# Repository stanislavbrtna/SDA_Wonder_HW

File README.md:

# SDA Mk. 2 Hardware Sources
In the Board directory are KiCad project files for the Boards used in the SDA and in the case Directory there are FreeCAD files for the SDA case. You can find more info about the SDA Project on its [project page](https://hackaday.io/project/35165-sda-the-best-new-pda) on hackaday.io.

## Known Bugs - Rev2b (current)

 1. SD card slot casing is not grounded on the pcb, sd card insertion detection doesn't work because of it. This can be fixed by scraping off the protective mask near the pin and bridging ground and shielding  with a bit of solder.
 2. Pads for battery connector are too small and can be ripped out of place when device falls form sufficient height. This is sort-of fixed with second revision of the case by giving the battery better support.
 3. The stacked PCBs are a point of failure, stress is built up in the connecting pins during soldering. This stress can break the contacts after few years of use, temperature changes, drops of the device. Luckily, re-soldering these pins is an easy job.

## Known Bugs - Rev1

 1. Vcc is used as Vref, if battery goes under 3.3V, then ADC measurements are wrong.
 2. There is no under-voltage protection at the moment.
 3. There is currently no guide for battery connector alignment, if battery connector is misaligned battery doesn't make good contact. 

## Case R2 notes
Second revision was printed and tested. It contains optional holes for a speaker and a microphone. The add-on module and cradle works well. 

## Case notes
 Only the 3D printable case for SDA was printed and tested, the FreeCAD file also contains drawings of a cradle and an add-on module, those are still work-in progress.

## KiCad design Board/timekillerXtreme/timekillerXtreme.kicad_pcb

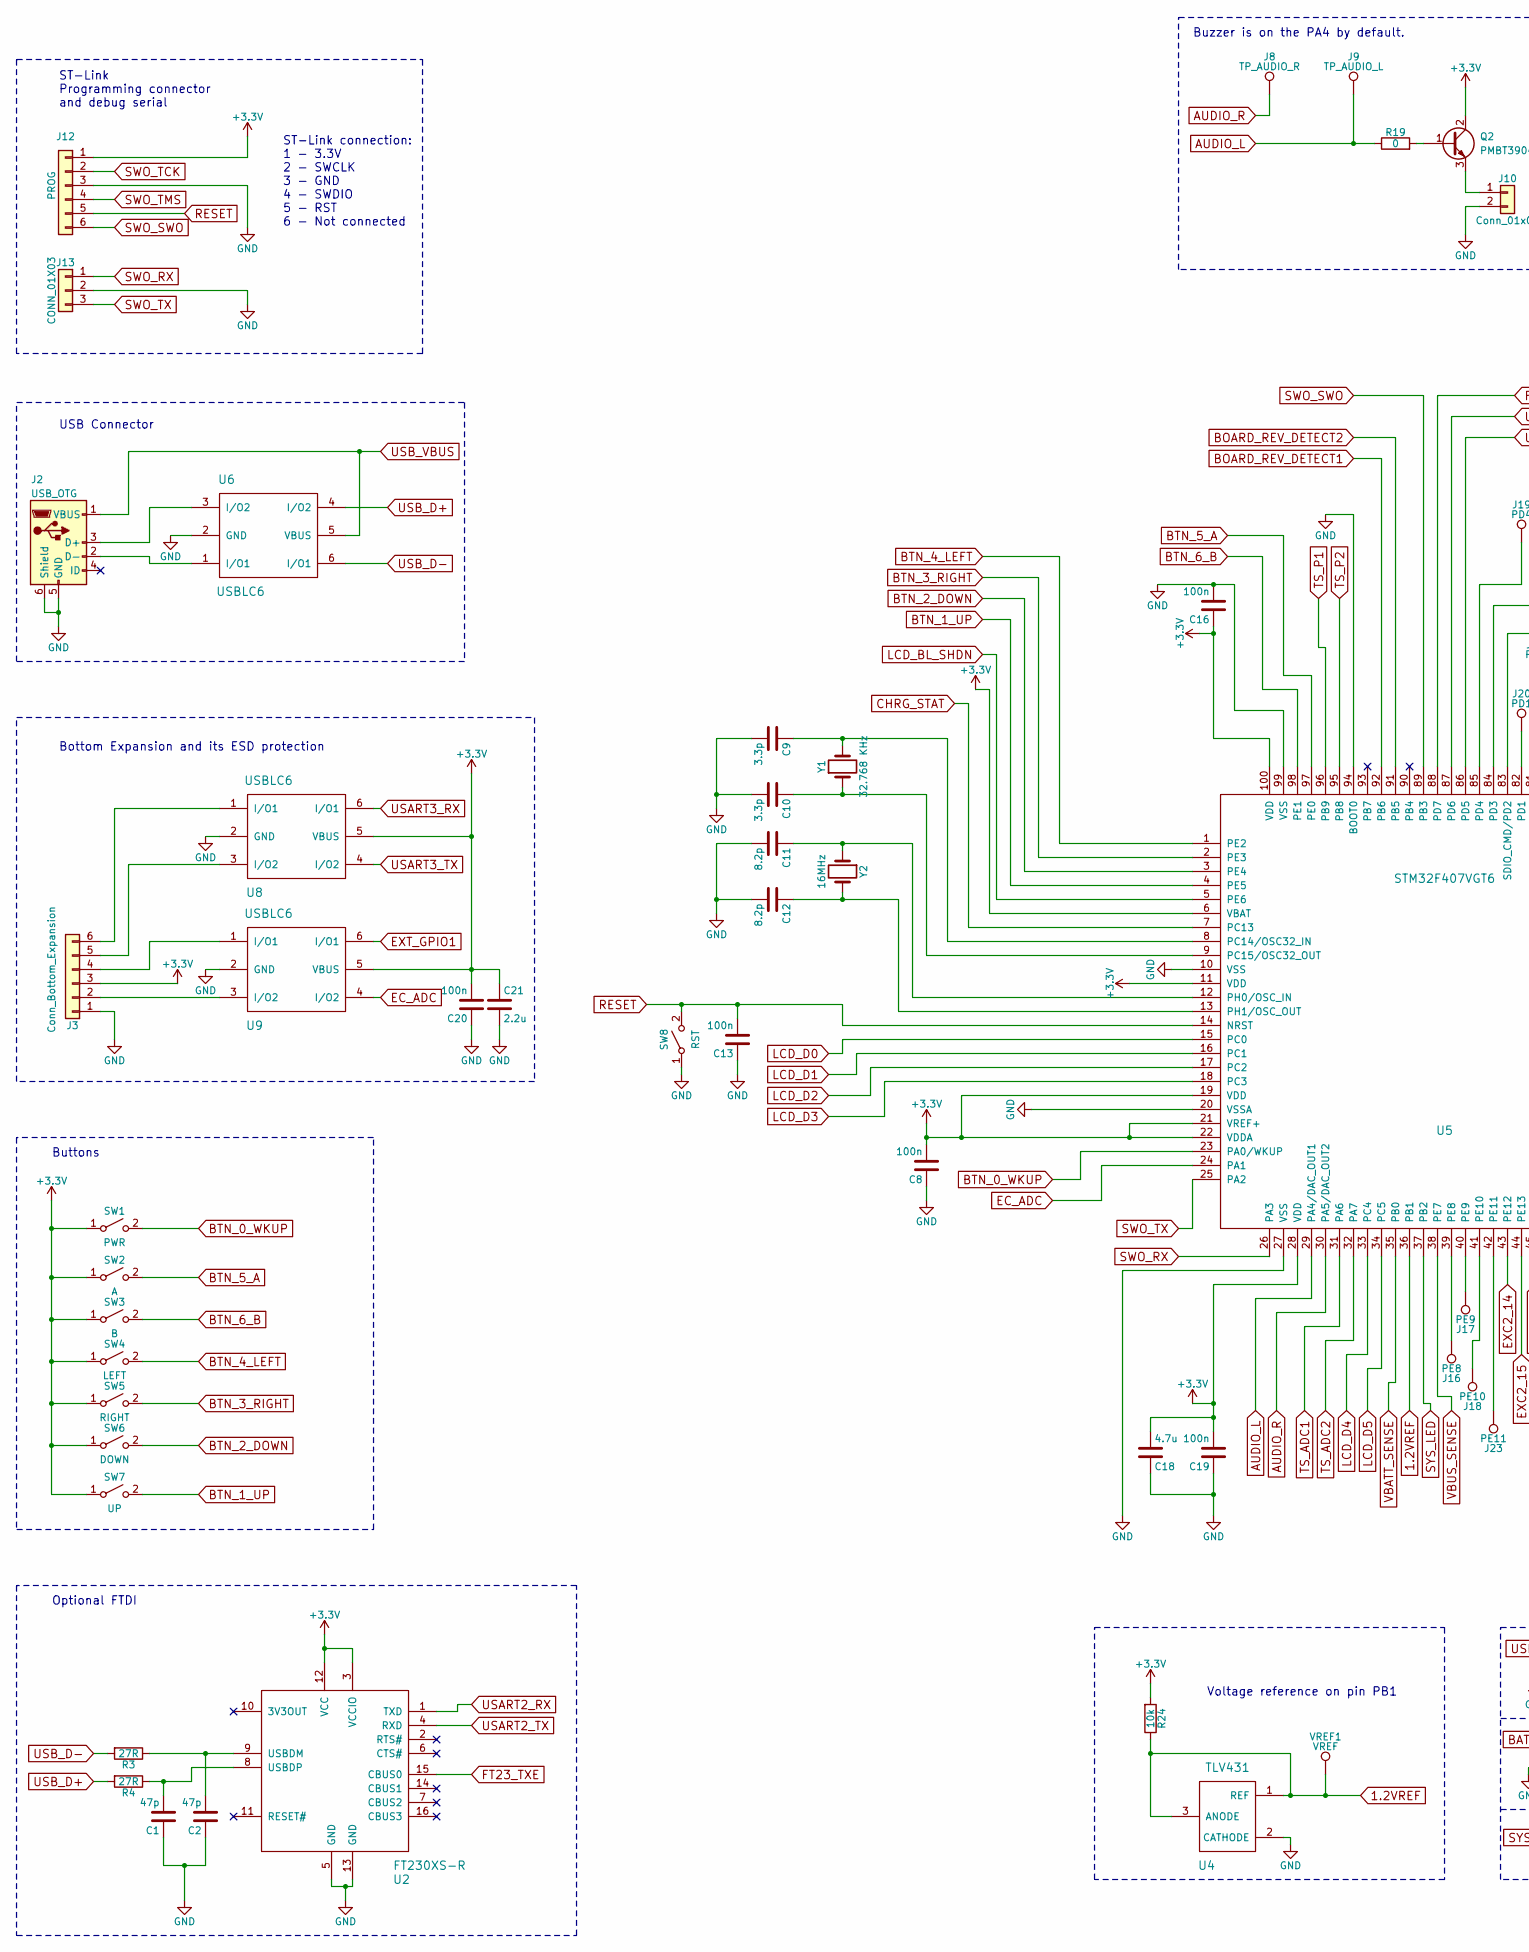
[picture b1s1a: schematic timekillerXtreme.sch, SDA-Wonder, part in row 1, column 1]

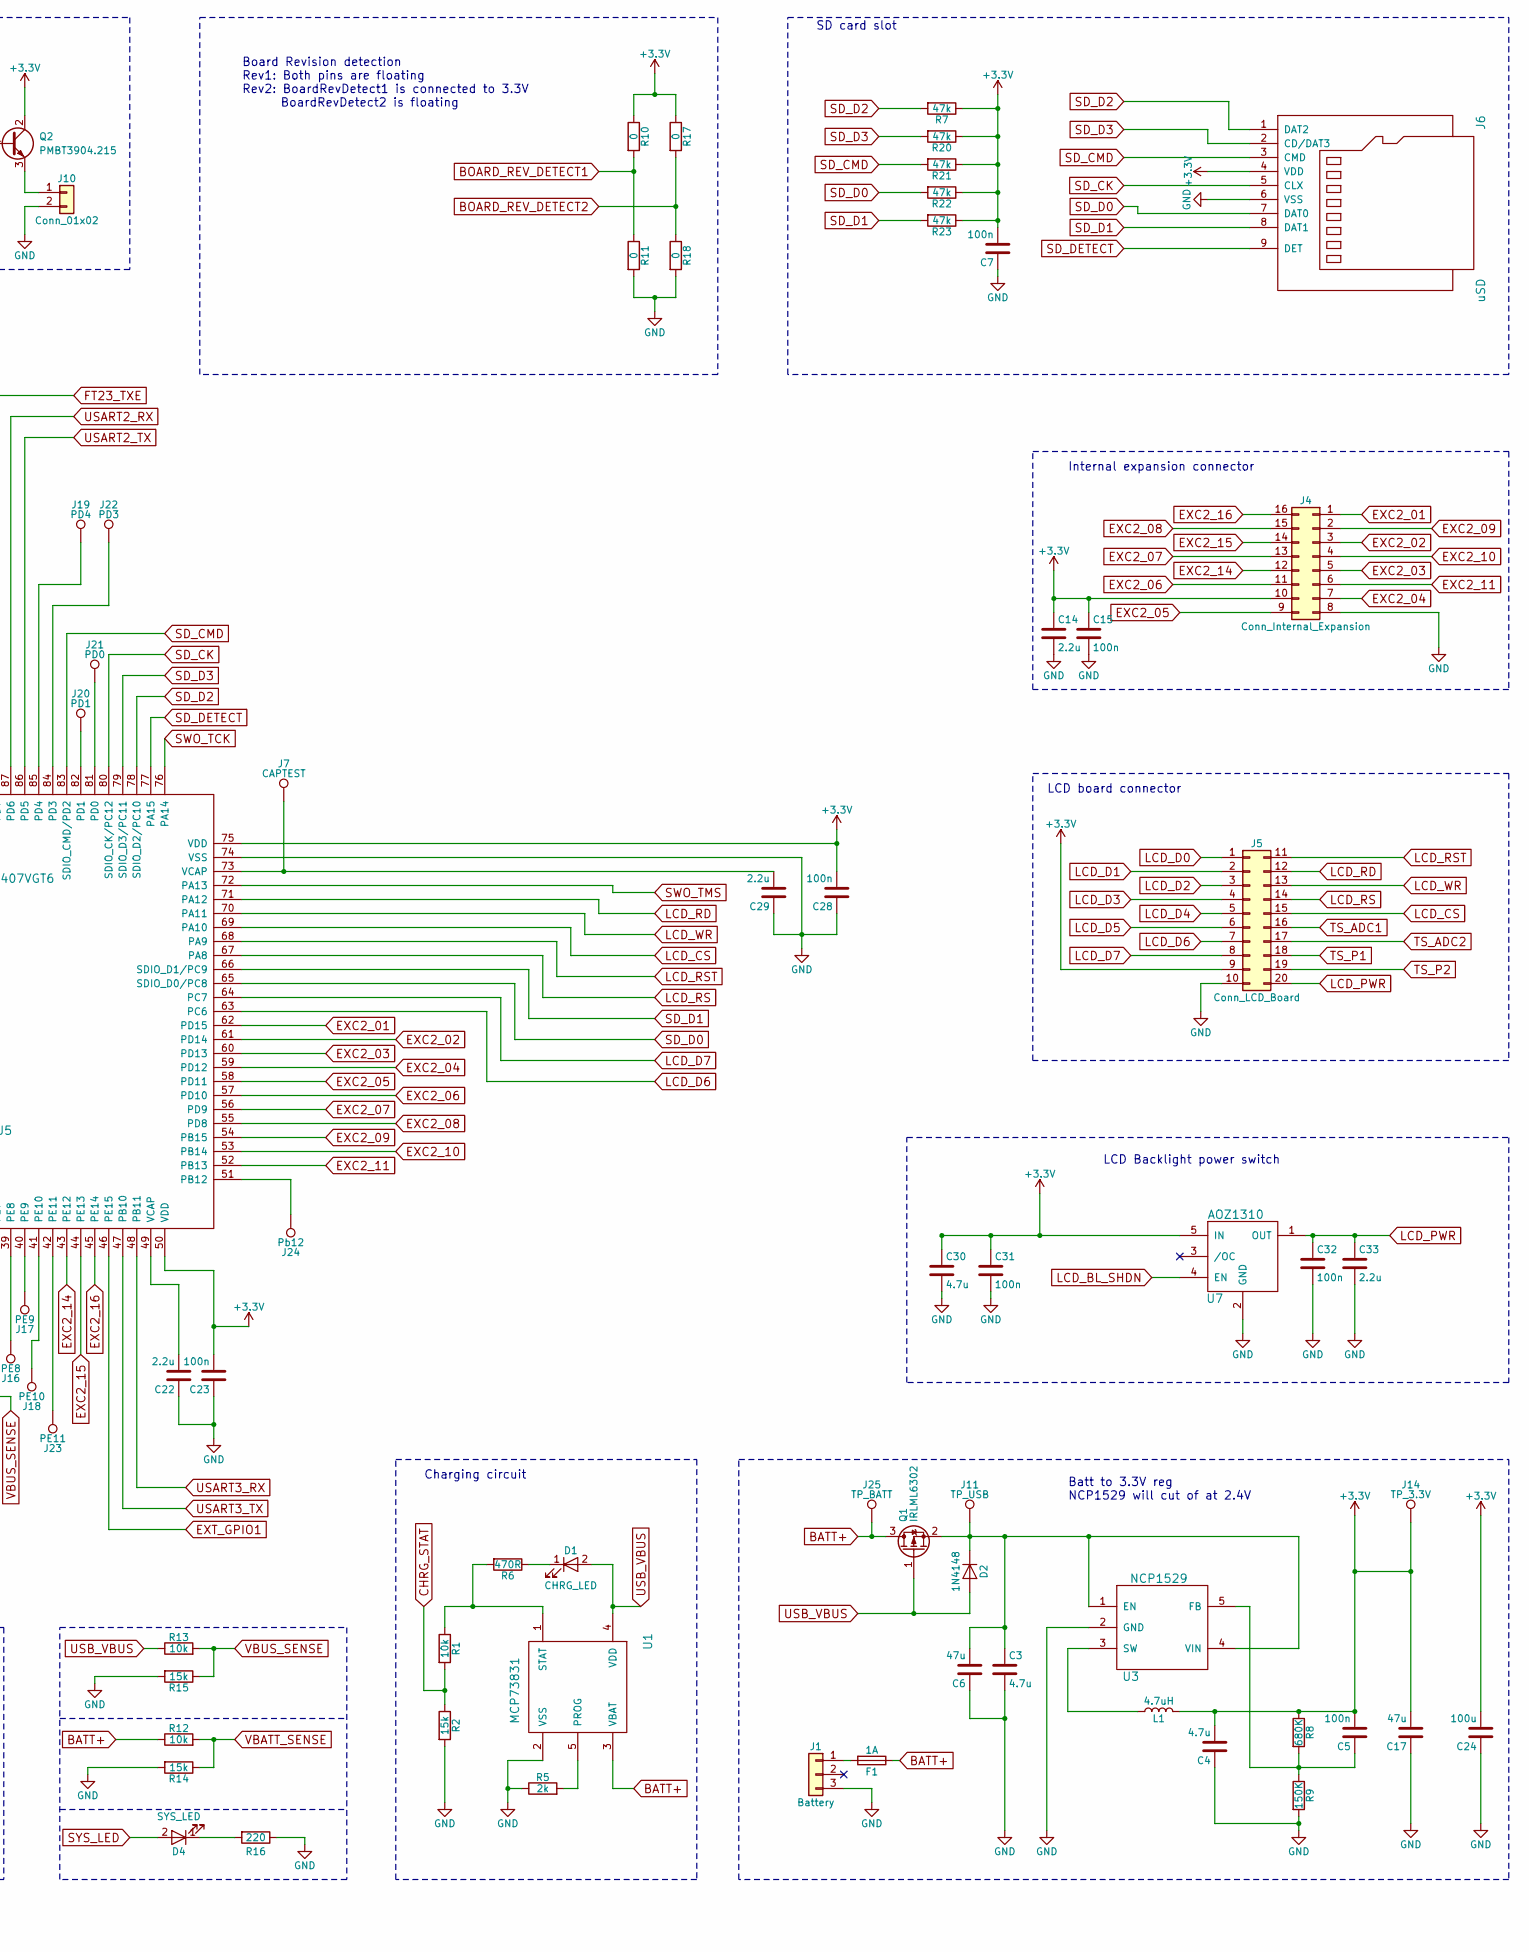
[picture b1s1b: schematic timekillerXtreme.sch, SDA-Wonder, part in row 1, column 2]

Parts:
C1, C2: 47p; C_0805_HandSoldering
C3, C4, C18, C30: 4.7u; C_0805_HandSoldering
C5, C7, C8, C13, C15, C16, C19, C20, C23, C28, C31, C32: 100n; C_0805_HandSoldering
C6, C17: 47u; C_1210_HandSoldering
C9, C10: 3.3p; C_0805_HandSoldering
C11, C12: 8.2p; C_0805_HandSoldering
C14, C21, C22, C29, C33: 2.2u; C_0805_HandSoldering
C24: 100u; C_1210_HandSoldering
D1: CHRG_LED; LED_D3.0mm_FlatTop
D2: 1N4148; D_MiniMELF
D4: SYS_LED; LED_D3.0mm_FlatTop
F1: 1A; R_0805_HandSoldering
J1: Battery; Conn_Nokia_BL-5C
J2: USB_OTG; USB_Micro-B-CircularHoles
J3: Conn_Bottom_Expansion; Pin_Header__1x06_Pitch2.54mm-NoSilk
J4: Conn_Internal_Expansion; Pin_Header_Straight_2x08_Pitch1.27mm
J5: Conn_LCD_Board; Pin_Header_Straight_2x10_Pitch2.00mm
J6: uSD; ATTEND-SD-TME
J7: CAPTEST; Measurement_Point_Round-SMD-Pad_Small
J8: TP_AUDIO_R; Measurement_Point_Round-SMD-Pad_Small
J9: TP_AUDIO_L; Measurement_Point_Round-SMD-Pad_Small
J10: Conn_01x02; Pin_Header_Straight_1x02_Pitch2.00mm
J11: TP_USB; Measurement_Point_Round-SMD-Pad_Small
J12: PROG; Pin_Header_Straight_1x06_Pitch1.27mm
J13: CONN_01X03; Pin_Header_Straight_1x03_Pitch1.27mm
J14: TP_3.3V; Measurement_Point_Round-SMD-Pad_Small
J16: PE8; Measurement_Point_Round-SMD-Pad_Small
J17: PE9; Measurement_Point_Round-SMD-Pad_Small
J18: PE10; Measurement_Point_Round-SMD-Pad_Small
J19: PD4; Measurement_Point_Round-SMD-Pad_Small
J20: PD1; Measurement_Point_Round-SMD-Pad_Small
J21: PD0; Measurement_Point_Round-SMD-Pad_Small
J22: PD3; Measurement_Point_Round-SMD-Pad_Small
J23: PE11; Measurement_Point_Round-SMD-Pad_Small
J24: Pb12; Measurement_Point_Round-SMD-Pad_Small
J25: TP_BATT; Measurement_Point_Round-SMD-Pad_Small
L1: 4.7uH; L4x4mm
Q1: IRLML6302; SOT-23_Handsoldering
Q2: PMBT3904.215; SOT-23_Handsoldering
R1, R12, R13, R24: 10k; R_0805_HandSoldering
R2, R14, R15: 15k; R_0805_HandSoldering
R3, R4: 27R; R_0805_HandSoldering
R5: 2k; R_0805_HandSoldering
R6: 470R; R_0805_HandSoldering
R7, R20, R21, R22, R23: 47k; R_0805_HandSoldering
R8: 680K; R_0805_HandSoldering
R9: 150K; R_0805_HandSoldering
R10, R11, R17, R18: 0; R_0603
R16: 220; R_0805_HandSoldering
R19: 0; R_0805_HandSoldering
SW1: PWR; SW_PUSH_6mm_h5mm
SW2: A; SW_PUSH_6mm_h5mm
SW3: B; SW_PUSH_6mm_h5mm
SW4: LEFT; SW_PUSH_6mm_h5mm
SW5: RIGHT; SW_PUSH_6mm_h5mm
SW6: DOWN; SW_PUSH_6mm_h5mm
SW7: UP; SW_PUSH_6mm_h5mm
SW8: RST; SW_PUSH_6mm_h4.3mm
U1: MCP73831; SOT-23-5_HandSoldering
U2: FT230XS-R; SSOP-16_5.3x6.2mm_Pitch0.65mm
U3: NCP1529; SOT-23-5_HandSoldering
U4: TLV431; TSOT-23
U5: STM32F407VGT6; LQFP-100_14x14mm_Pitch0.5mm
U6, U8, U9: USBLC6; SOT-23-6_Handsoldering
U7: AOZ1310; SOT-23-5_HandSoldering
VREF1: VREF; Measurement_Point_Round-SMD-Pad_Small
Y1: 32.768 KHz; xtall_epso_mc146
Y2: 16MHz; Crystal_SMD_HC49-HS-mini

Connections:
AUDIO_L: J9.1, R19.1, U5.29 (PA4/DAC_OUT1)
AUDIO_R: J8.1, U5.30 (PA5/DAC_OUT2)
BATT+: F1.1, J25.1, Q1.3 (D), R12.1, U1.3 (VBAT); also elsewhere on the board
BOARD_REV_DETECT1: R10.2, R11.1, U5.92 (PB6)
BOARD_REV_DETECT2: R17.2, R18.1, U5.91 (PB5)
BTN_0_WKUP: SW1.2 (B), U5.23 (PA0/WKUP)
BTN_1_UP: SW7.2 (B), U5.4 (PE5)
BTN_2_DOWN: SW6.2 (B), U5.3 (PE4)
BTN_3_RIGHT: SW5.2 (B), U5.2 (PE3)
BTN_4_LEFT: SW4.2 (B), U5.1 (PE2)
BTN_5_A: SW2.2 (B), U5.97 (PE0)
BTN_6_B: SW3.2 (B), U5.98 (PE1)
CHRG_STAT: R1.2, R2.1, U5.7 (PC13)
EC_ADC: U5.24 (PA1), U9.4 (I/O2)
EXC2_01: J4.1, U5.62 (PD15); also elsewhere on the board
EXC2_02: J4.3, U5.61 (PD14); also elsewhere on the board
EXC2_03: J4.5, U5.60 (PD13); also elsewhere on the board
EXC2_04: J4.7, U5.59 (PD12); also elsewhere on the board
EXC2_05: J4.9, U5.58 (PD11); also elsewhere on the board
EXC2_06: J4.11, U5.57 (PD10); also elsewhere on the board
EXC2_07: J4.13, U5.56 (PD9); also elsewhere on the board
EXC2_08: J4.15, U5.55 (PD8); also elsewhere on the board
EXC2_09: J4.2, U5.54 (PB15); also elsewhere on the board
EXC2_10: J4.4, U5.53 (PB14); also elsewhere on the board
EXC2_11: J4.6, U5.52 (PB13); also elsewhere on the board
EXC2_14: J4.12, U5.43 (PE12); also elsewhere on the board
EXC2_15: J4.14, U5.44 (PE13); also elsewhere on the board
EXC2_16: J4.16, U5.45 (PE14); also elsewhere on the board
EXT_GPIO1: U5.46 (PE15), U9.6 (I/O1)
FT23_TXE: U2.15 (CBUS0), U5.88 (PD7)
GND: C1.1, C2.1, C3.2, C4.1, C6.1, C7.1, C8.1, C9.2, C10.2, C11.2, C12.2, C13.1, C14.2, C15.2, C16.2, C17.1, C18.1, C19.1, C20.1, C21.2, C22.1, C23.1, C24.1, C28.1, C29.1, C30.2, C31.2, C32.2, C33.2, J1.3, J2.5 (GND), J2.6 (Shield), J3.1, J4.8, J5.10, J6.6 (VSS), J10.2, J12.3, J13.2, R2.2, R5.1, R9.2, R11.2, R14.2, R15.2, R16.1, R18.2, SW8.1 (A), U1.2 (VSS), U2.5 (GND), U2.13 (GND), U3.2 (GND), U4.2 (CATHODE), U5.10 (VSS), U5.20 (VSSA), U5.27 (VSS), U5.74 (VSS), U5.94 (BOOT0), U5.99 (VSS), U6.2 (GND), U7.2 (GND), U8.2 (GND), U9.2 (GND); also elsewhere on the board
LCD_BL_SHDN: U5.5 (PE6), U7.4 (EN)
LCD_CS: J5.15, U5.69 (PA10)
LCD_D0: J5.1, U5.15 (PC0)
LCD_D1: J5.2, U5.16 (PC1)
LCD_D2: J5.3, U5.17 (PC2)
LCD_D3: J5.4, U5.18 (PC3)
LCD_D4: J5.5, U5.33 (PC4)
LCD_D5: J5.6, U5.34 (PC5)
LCD_D6: J5.7, U5.63 (PC6)
LCD_D7: J5.8, U5.64 (PC7)
LCD_PWR: C32.1, C33.1, J5.20, U7.1 (OUT)
LCD_RD: J5.12, U5.71 (PA12)
LCD_RS: J5.14, U5.67 (PA8)
LCD_RST: J5.11, U5.68 (PA9)
LCD_WR: J5.13, U5.70 (PA11)
unnamed: C1.2, R4.1, U2.8 (USBDP)
unnamed: C2.2, R3.1, U2.9 (USBDM)
unnamed 48: C3.1, C6.2, D2.1 (K), J11.1, Q1.2 (S), U3.1 (EN), U3.4 (VIN); also elsewhere on the board
unnamed: C5.1, R8.2, R9.1, U3.5 (FB)
unnamed: C9.1, U5.8 (PC14/OSC32_IN), Y1.2
unnamed: C10.1, U5.9 (PC15/OSC32_OUT), Y1.1
unnamed: C11.1, U5.12 (PH0/OSC_IN), Y2.1
unnamed: C12.1, U5.13 (PH1/OSC_OUT), Y2.2
unnamed: C22.2, U5.49 (VCAP)
unnamed 55: C29.2, J7.1, U5.73 (VCAP); also elsewhere on the board
unnamed: D1.1 (K), R6.1
unnamed: D4.1 (K), R16.2
unnamed: F1.2, J1.1
unnamed: J2.2 (D-), U6.1 (I/O1)
unnamed: J2.3 (D+), U6.3 (I/O2)
unnamed: J3.2, U9.3 (I/O2)
unnamed: J3.4, U9.1 (I/O1)
unnamed: J3.5, U8.3 (I/O2)
unnamed: J3.6, U8.1 (I/O1)
unnamed 67: J10.1, Q2.3 (E); also elsewhere on the board
unnamed: J16.1, U5.39 (PE8)
unnamed: J17.1, U5.40 (PE9)
unnamed: J18.1, U5.41 (PE10)
unnamed: J19.1, U5.85 (PD4)
unnamed: J20.1, U5.82 (PD1)
unnamed: J21.1, U5.81 (PD0)
unnamed: J22.1, U5.84 (PD3)
unnamed: J23.1, U5.42 (PE11)
unnamed: J24.1, U5.51 (PB12)
unnamed: L1.1, U3.3 (SW)
unnamed: Q2.1 (B), R19.2
unnamed: R1.1, R6.2, U1.1 (STAT)
unnamed: R5.2, U1.5 (PROG)
RESET: C13.2, J12.5, SW8.2 (B), U5.14 (NRST); also elsewhere on the board
SD_CK: J6.5 (CLX), U5.80 (SDIO_CK/PC12)
SD_CMD: J6.3 (CMD), R21.2, U5.83 (SDIO_CMD/PD2)
SD_D0: J6.7 (DAT0), R22.2, U5.65 (SDIO_D0/PC8)
SD_D1: J6.8 (DAT1), R23.2, U5.66 (SDIO_D1/PC9)
SD_D2: J6.1 (DAT2), R7.2, U5.78 (SDIO_D2/PC10)
SD_D3: J6.2 (CD/DAT3), R20.2, U5.79 (SDIO_D3/PC11)
SD_DETECT: J6.9 (DET), U5.77 (PA15)
SWO_RX: J13.1, U5.26 (PA3)
SWO_SWO: J12.6, U5.89 (PB3); also elsewhere on the board
SWO_TCK: J12.2, U5.76 (PA14); also elsewhere on the board
SWO_TMS: J12.4, U5.72 (PA13); also elsewhere on the board
SWO_TX: J13.3, U5.25 (PA2)
SYS_LED: D4.2 (A), U5.37 (PB2)
TS_ADC1: J5.16, U5.31 (PA6)
TS_ADC2: J5.17, U5.32 (PA7)
TS_P1: J5.18, U5.96 (PB9)
TS_P2: J5.19, U5.95 (PB8)
USART2_RX: U2.1 (TXD), U5.87 (PD6)
USART2_TX: U2.4 (RXD), U5.86 (PD5)
USART3_RX: U5.48 (PB11), U8.6 (I/O1)
USART3_TX: U5.47 (PB10), U8.4 (I/O2)
USB_D+: R4.2, U6.4 (I/O2)
USB_D-: R3.2, U6.6 (I/O1)
USB_VBUS: D1.2 (A), D2.2 (A), J2.1 (VBUS), Q1.1 (G), R13.1, U1.4 (VDD), U6.5 (VBUS)
VBATT_SENSE: R12.2, R14.1, U5.35 (PB0)
VBUS_SENSE: R13.2, R15.1, U5.38 (PE7)

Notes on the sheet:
ST-Link Programming connector and debug serial
Board Revision detection Rev1: Both pins are floating Rev2: BoardRevDetect1 is connected to 3.3V BoardRevDetect2 is floating
Buzzer is on the PA4 by default.
LCD Backlight power switch
SD card slot
Internal expansion connector
LCD board connector
Bottom Expansion and its ESD protection
Batt to 3.3V reg NCP1529 will cut of at 2.4V
Charging circuit
USB Connector
Optional FTDI
Buttons
Voltage reference on pin PB1
ST-Link connection: 1 - 3.3V 2 - SWCLK 3 - GND 4 - SWDIO 5 - RST 6 - Not connected

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
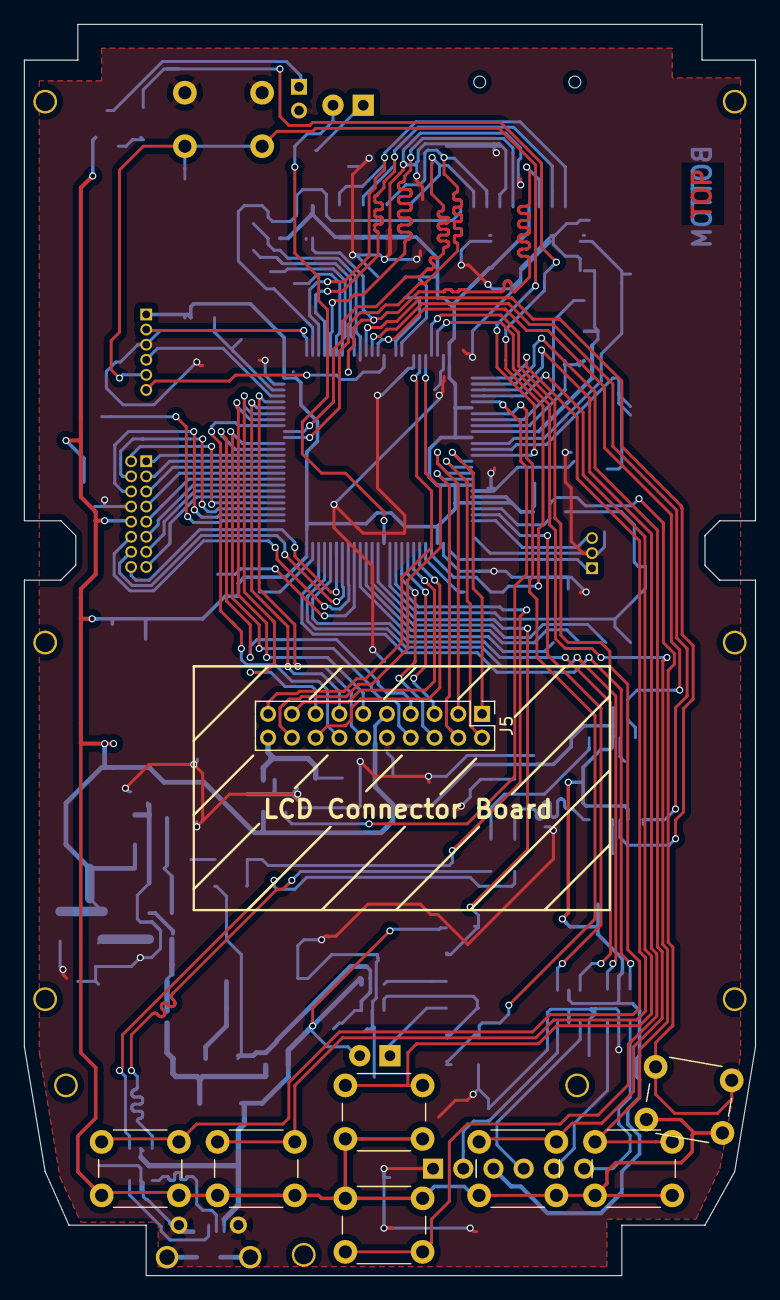
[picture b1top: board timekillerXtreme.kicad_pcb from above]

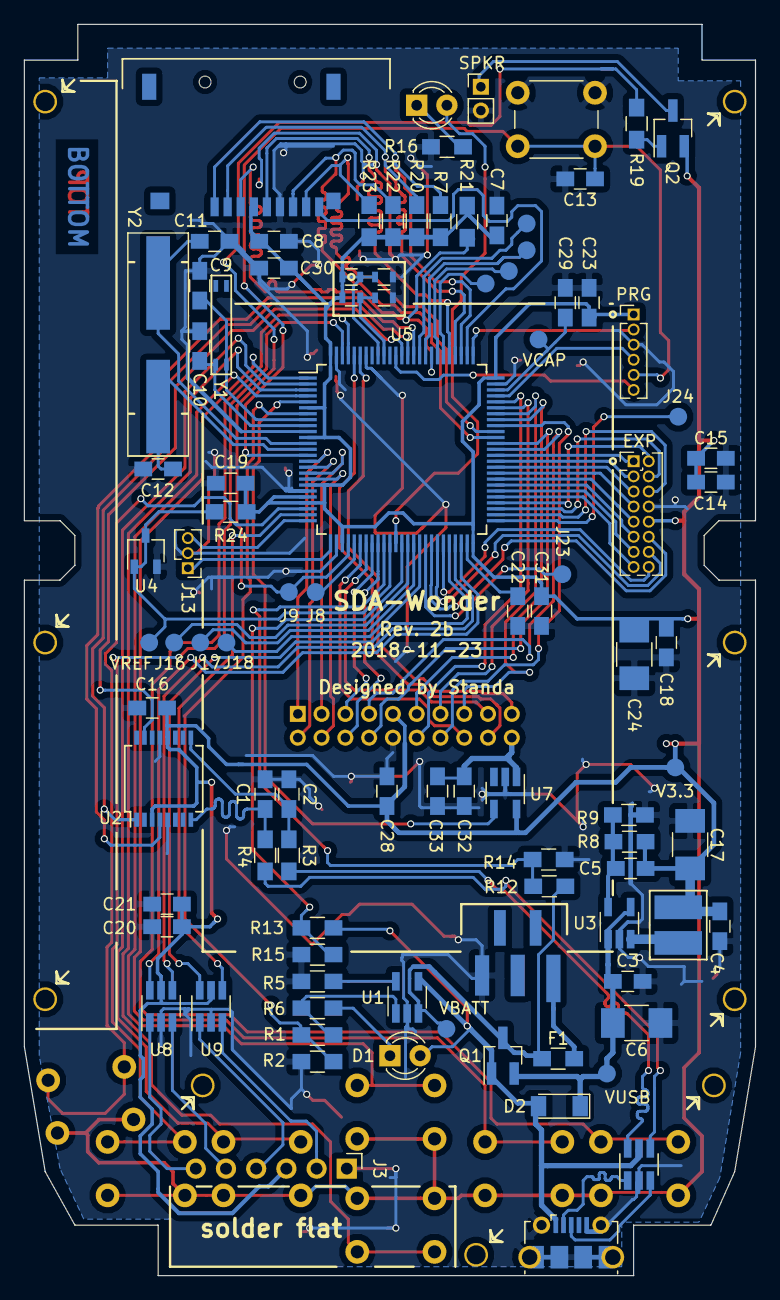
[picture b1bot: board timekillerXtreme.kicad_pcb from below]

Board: 2 copper layers, 61.5 x 105.2 mm, 105 parts (97 on the bottom side), 108 nets.

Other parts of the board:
EXP: Conn_Internal_Expansion; Pin_Header_Straight_2x08_Pitch1.27mm
PRG: PROG; Pin_Header_Straight_1x06_Pitch1.27mm
SPKR: Conn_01x02; Pin_Header_Straight_1x02_Pitch2.00mm
V3.3: TP_3.3V; Measurement_Point_Round-SMD-Pad_Small
VBATT: TP_BATT; Measurement_Point_Round-SMD-Pad_Small
VCAP: VCAP; Measurement_Point_Round-SMD-Pad_Small
VREF: VREF; Measurement_Point_Round-SMD-Pad_Small
VUSB: TP_USB; Measurement_Point_Round-SMD-Pad_Small

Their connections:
BATT+: VBATT.1; also elsewhere on the board
EXC2_01: EXP.1; also elsewhere on the board
EXC2_02: EXP.3; also elsewhere on the board
EXC2_03: EXP.5; also elsewhere on the board
EXC2_04: EXP.7; also elsewhere on the board
EXC2_05: EXP.9; also elsewhere on the board
EXC2_06: EXP.11; also elsewhere on the board
EXC2_07: EXP.13; also elsewhere on the board
EXC2_08: EXP.15; also elsewhere on the board
EXC2_09: EXP.2; also elsewhere on the board
EXC2_10: EXP.4; also elsewhere on the board
EXC2_11: EXP.6; also elsewhere on the board
EXC2_14: EXP.12; also elsewhere on the board
EXC2_15: EXP.14; also elsewhere on the board
EXC2_16: EXP.16; also elsewhere on the board
GND: EXP.8, PRG.3, SPKR.2; also elsewhere on the board
unnamed 48: VUSB.1; also elsewhere on the board
unnamed 55: VCAP.1; also elsewhere on the board
unnamed 67: SPKR.1; also elsewhere on the board
RESET: PRG.5; also elsewhere on the board
SWO_SWO: PRG.6; also elsewhere on the board
SWO_TCK: PRG.2; also elsewhere on the board
SWO_TMS: PRG.4; also elsewhere on the board

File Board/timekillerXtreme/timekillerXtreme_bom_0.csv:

Component,Description,Part,References,Value,Footprint,Quantity Per PCB,Datasheet,TME_Part_number
1,Unpolarized capacitor,C,C5 C8 C13 C16 C19 C23 C28 C31 C32,100n,C_0805_HandSoldering,9,,
2,Unpolarized capacitor,C,C22 C29 C33,2.2u,C_0805_HandSoldering,3,,
3,Unpolarized capacitor,C,C3 C4 C30,4.7u,C_0805_HandSoldering,3,,
4,Unpolarized capacitor,C,C1 C2,47p,C_0805_HandSoldering,2,,
5,Unpolarized capacitor,C,C6 C17,47u,C_1210_HandSoldering,2,,
6,Unpolarized capacitor,C,C9 C10,4p,C_0805_HandSoldering,2,,
7,Unpolarized capacitor,C,C11 C12,8p,C_0805_HandSoldering,2,,
8,Diode,D,D2,1N4148,D_MiniMELF_Handsoldering,1,,
9,LED generic,LED,D1,CHRG_LED,LED_D3.0mm_FlatTop,1,,
10,LED generic,LED,D4,SYS_LED,LED_D3.0mm_FlatTop,1,,
11,"Generic connector, single row, 01x03",Conn_01x03,J1,Battery,Conn_Nokia_BL-5C,1,,
12,point,TEST_1P,J7,CAPTEST,Measurement_Point_Round-SMD-Pad_Small,1,,
13,"Generic connector, single row, 01x03",Conn_01x03,J13,CONN_01X03,Pin_Header_Straight_1x03_Pitch1.27mm,1,,
14,"Generic connector, single row, 01x02",Conn_01x02,J10,Conn_01x02,Pin_Header_Straight_1x02_Pitch2.00mm,1,,
15,"Generic connector, single row, 01x06",Conn_01x06,J3,Conn_Bottom_Expansion,Pin_Header__1x06_Pitch2.54mm-NoSilk,1,,
16,"Generic connector, double row, 02x08, counter clockwise pin numbering scheme (similar to DIP packge numbering)",Conn_02x08_Counter_Clockwise,J4,Conn_Internal_Expansion,Pin_Header_Straight_2x08_Pitch1.27mm,1,,
17,"Generic connector, double row, 02x10, top/bottom pin numbering scheme (row 1: 1...pins_per_row, row2: pins_per_row+1 ... num_pins)",Conn_02x10_Top_Bottom,J5,Conn_LCD_Board,Pin_Header_Straight_2x10_Pitch2.00mm,1,,
18,point,TEST_1P,J21,PD0,Measurement_Point_Round-SMD-Pad_Small,1,,
19,point,TEST_1P,J20,PD1,Measurement_Point_Round-SMD-Pad_Small,1,,
20,point,TEST_1P,J22,PD3,Measurement_Point_Round-SMD-Pad_Small,1,,
21,point,TEST_1P,J19,PD4,Measurement_Point_Round-SMD-Pad_Small,1,,
22,point,TEST_1P,J18,PE10,Measurement_Point_Round-SMD-Pad_Small,1,,
23,point,TEST_1P,J23,PE11,Measurement_Point_Round-SMD-Pad_Small,1,,
24,point,TEST_1P,J15,PE7,Measurement_Point_Round-SMD-Pad_Small,1,,
25,point,TEST_1P,J16,PE8,Measurement_Point_Round-SMD-Pad_Small,1,,
26,point,TEST_1P,J17,PE9,Measurement_Point_Round-SMD-Pad_Small,1,,
27,"Generic connector, single row, 01x06",Conn_01x06,J12,PROG,Pin_Header_Straight_1x06_Pitch1.27mm,1,,
28,point,TEST_1P,J24,Pb12,Measurement_Point_Round-SMD-Pad_Small,1,,
29,point,TEST_1P,J14,TP_3.3V,Measurement_Point_Round-SMD-Pad_Small,1,,
30,point,TEST_1P,J9,TP_AUDIO_L,Measurement_Point_Round-SMD-Pad_Small,1,,
31,point,TEST_1P,J8,TP_AUDIO_R,Measurement_Point_Round-SMD-Pad_Small,1,,
32,point,TEST_1P,J25,TP_BATT,Measurement_Point_Round-SMD-Pad_Small,1,,
33,point,TEST_1P,J11,TP_USB,Measurement_Point_Round-SMD-Pad_Small,1,,
34,USB mini/micro connector,USB_OTG,J2,USB_OTG,USB_Micro-B-CircularHoles,1,,
35,,uSD-RESCUE-timekillerXtreme,J6,uSD,ATTEND-SD-TME,1,,ATTEND 112J-TDAR-R01
36,Inductor,L,L1,4.7uH,L4x4mm,1,,
37,"-60V Vds, -0.18A Id, P-Channel MOSFET, SOT-23-3",NTR2101P,Q1,IRLML6302,SOT-23,1,http://www.vishay.com/docs/70209/70209.pdf,
38,Transistor NPN (general),Q_NPN_BCE,Q2,PMBT3904.215,SOT-23,1,,
39,Resistor,R,R10 R11 R17 R18,0,R_0603,4,,
40,Resistor,R,R19,0,R_0805_HandSoldering,1,,
41,Resistor,R,R1 R12 R13,10k,R_0805_HandSoldering,3,,
42,Resistor,R,R9,150K,R_0805_HandSoldering,1,,
43,Resistor,R,R2 R14 R15,15k,R_0805_HandSoldering,3,,
44,Resistor,R,R16,220,R_0805_HandSoldering,1,,
45,Resistor,R,R3 R4,27R,R_0805_HandSoldering,2,,
46,Resistor,R,R5,2k,R_0805_HandSoldering,1,,
47,Resistor,R,R6,470R,R_0805_HandSoldering,1,,
48,Resistor,R,R7 R20 R21 R22 R23,47k,R_0805_HandSoldering,5,,
49,Resistor,R,R8,680K,R_0805_HandSoldering,1,,
50,Single Pole Single Throw (SPST) switch,SW_SPST,SW2,A,SW_PUSH_6mm_h5mm,1,,
51,Single Pole Single Throw (SPST) switch,SW_SPST,SW3,B,SW_PUSH_6mm_h5mm,1,,
52,Single Pole Single Throw (SPST) switch,SW_SPST,SW6,DOWN,SW_PUSH_6mm_h5mm,1,,
53,Single Pole Single Throw (SPST) switch,SW_SPST,SW4,LEFT,SW_PUSH_6mm_h5mm,1,,
54,Single Pole Single Throw (SPST) switch,SW_SPST,SW1,PWR,SW_PUSH_6mm_h5mm,1,,
55,Single Pole Single Throw (SPST) switch,SW_SPST,SW5,RIGHT,SW_PUSH_6mm_h5mm,1,,
56,Single Pole Single Throw (SPST) switch,SW_SPST,SW8,RST,SW_PUSH_6mm_h4.3mm,1,,
57,Single Pole Single Throw (SPST) switch,SW_SPST,SW7,UP,SW_PUSH_6mm_h5mm,1,,
58,"Cmos switch, SOT23-5",AOZ1310,U7,AOZ1310,SOT-23-5_HandSoldering,1,,
59,,FT230XS-R,U2,FT230XS-R,SSOP-16_5.3x6.2mm_Pitch0.65mm,1,,
60,,MCP73831,U1,MCP73831,SOT-23-5,1,,
61,,NCP1529,U3,NCP1529,SOT-23-5,1,,
62,,STM32F407VGT6,U5,STM32F407VGT6,LQFP-100_14x14mm_Pitch0.5mm,1,,
63,,USBLC6,U6 U8 U9,USBLC6,SOT-23-6_Handsoldering,3,,
64,Two pin crystal,Crystal,Y2,16MHz,Crystal_SMD_HC49-HS-mini,1,,
65,Two pin crystal,Crystal,Y1,32.768 KHz,xtall_epso_mc146,1,,





Component Groups:,65
Component Count:,95
Fitted Components:,95
Number of PCBs:,1
Total components:,95
Schematic Version:,0
Schematic Date:,2017-06-25
BoM Date:,"So13.jen2018,20:37:53CEST"
Schematic Source:,/home/stanislaw/SDA/2.0 Wonder/Board/timekillerXtreme/timekillerXtreme.sch
KiCad Version:,Eeschema 4.0.7-e2-6376~58~ubuntu16.04.1

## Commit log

2018-08-31 Initial commit.
2018-09-03 LCD connector board added.
2018-09-03 Board: SD slot moved, usb-conn changed from slots to holes. LCD board polished. Repo cleaned up.
2018-09-03 pcbs polished a bit. Case bottom pcb clearance enlarged.
2018-09-03 Daily commit 3.9.2018: sd moved to the right position (hopefully). minor case tweaks.
2018-09-04 SD card slot moved a bit again.
2018-09-06 system board polished, lcd flex connector footprint updated.
2018-09-06 Silkscreen fixed. Some minor tweaks.
2018-10-14 First round of modifications for rev.1
2018-10-22 Keeping repo up to date.
2018-10-30 Rev. 1 updates.
2018-10-30 Readme added.
2018-10-31 Readme updated.
2018-11-07 board & schematics updated
2018-11-14 Case and board updated, this will be shipped to the boardhouse and I will call it rev2 if it is ok.
2018-11-16 Vref fixed, board was sent to boardhouse.
2018-11-19 Schematics date and revision synced wit board. Misc case updates.
2018-11-23 PCB fixes after Rev2 assembly, new assembly docs added.
2018-11-26 Rev2 merged, readme updated
2019-01-21 Back adjusted so they doesn't interfere with sd card slot.
2023-05-09 added second revision of the case
2023-07-02 Back geometry fixed
2023-07-03 Second revision of the case finalized
2023-07-03 Docs updated
2023-07-03 stylus errors fixed
